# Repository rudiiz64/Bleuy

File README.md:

A design for a Bluetooth capable board.

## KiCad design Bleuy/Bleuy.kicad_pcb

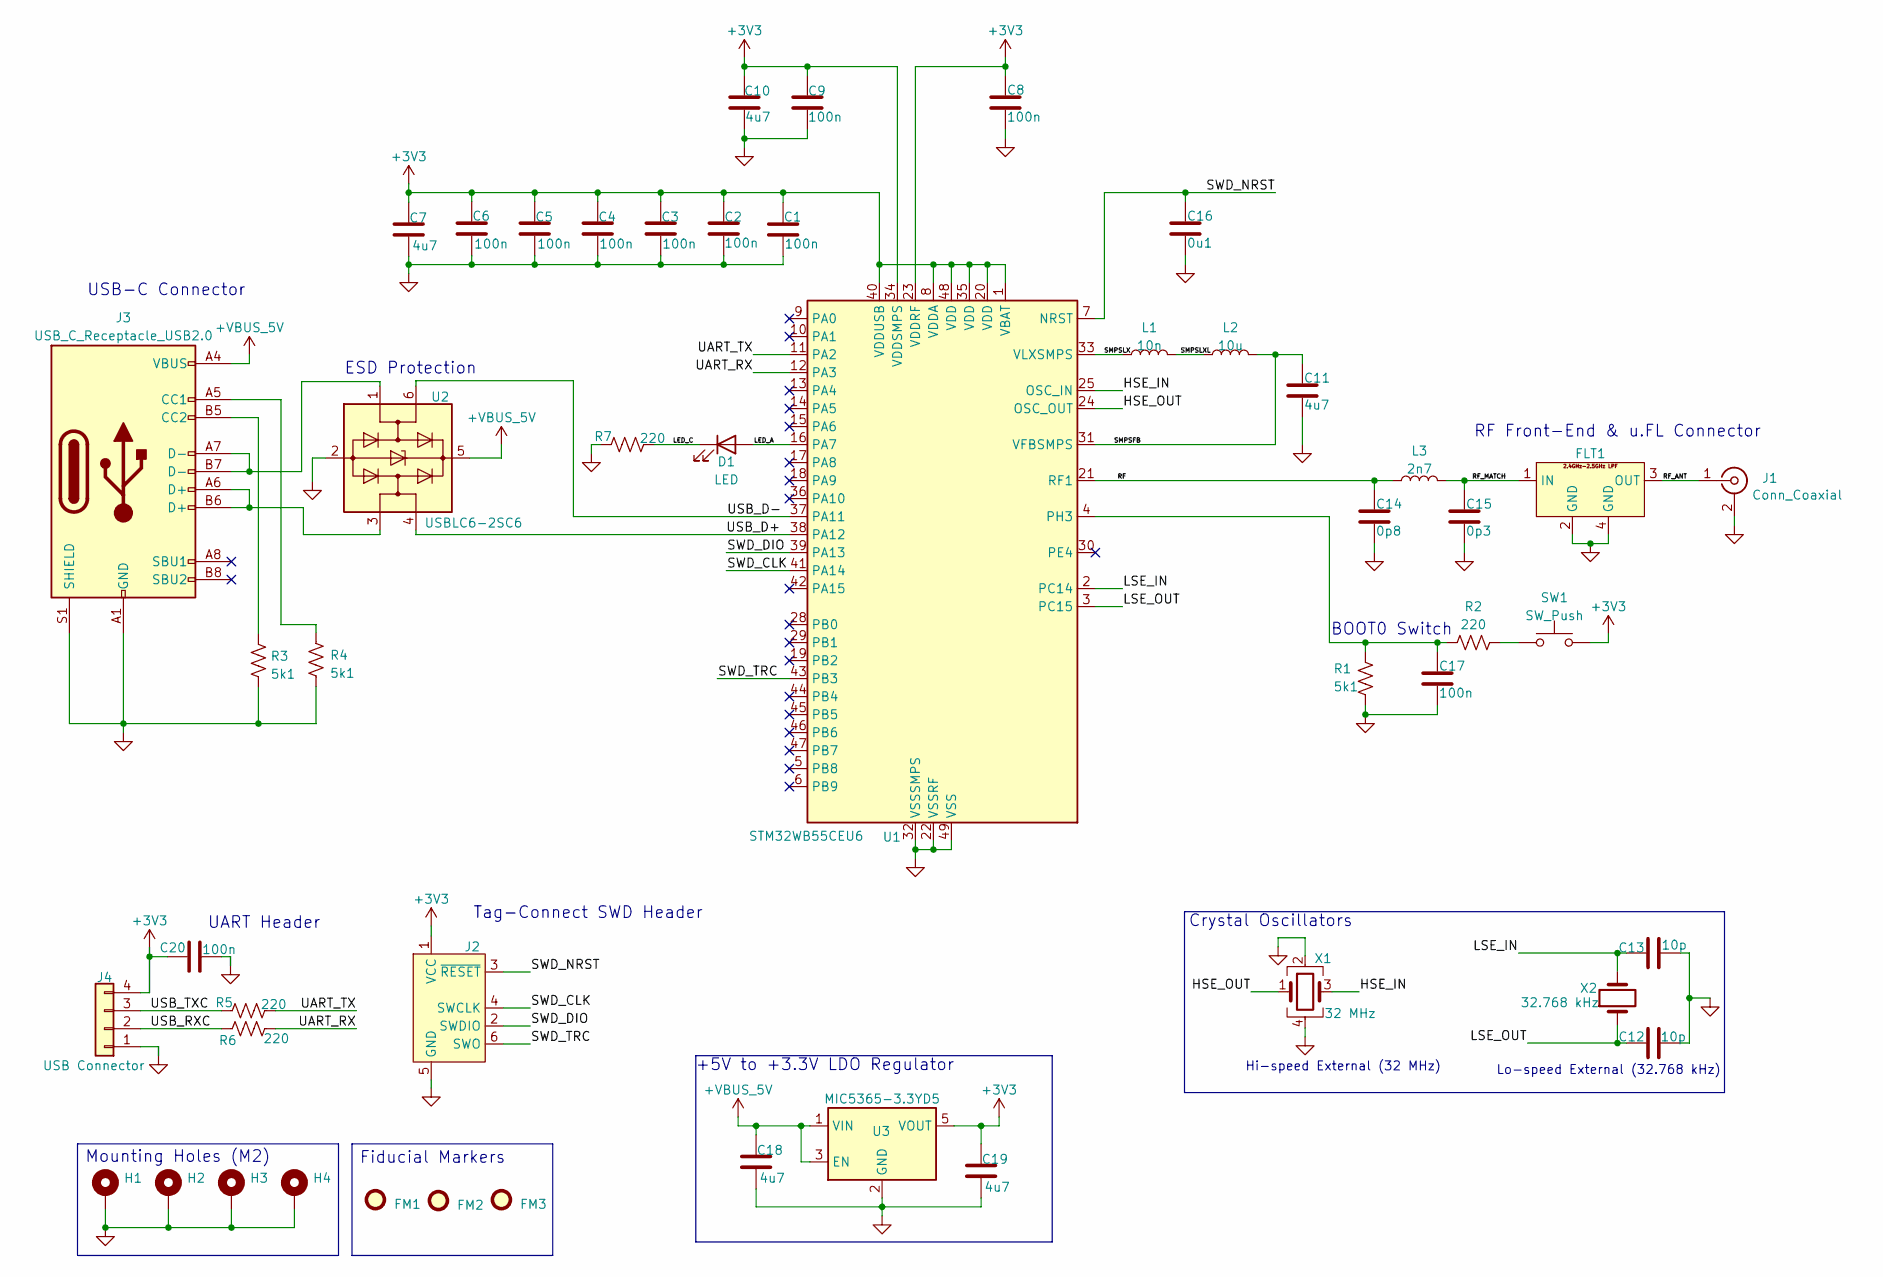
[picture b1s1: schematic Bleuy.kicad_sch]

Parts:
C1, C2, C3, C4, C5, C6, C8, C9, C17, C20: 100n; C_0402_1005Metric; Manufacturer Part Number 04023C104KAT2A
C7, C10, C11, C18, C19: 4u7; C_0603_1608Metric; Manufacturer Part Number 0603YD475MAT2A
C12, C13: 10p; C_0402_1005Metric; Manufacturer Part Number 04025A100JAT4A
C14: 0p8; C_0402_1005Metric; Manufacturer Part Number GRM1555C1HR80BA01D
C15: 0p3; C_0402_1005Metric; Manufacturer Part Number GRM1555C1HR30WA01D
C16: 0u1; C_0402_1005Metric; Manufacturer Part Number 04023C104KAT2A
D1: LED; LED_0402_1005Metric; Manufacturer Part Number 150040RS73240
FLT1: DLF162500LT-5028A1; Manufacturer Part Number DLF162500LT-5028A1
FM1, FM2, FM3: Fiducial; Fiducial_1mm_Mask2mm
H1, H2, H3, H4: MountingHole_Pad; MountingHole_2.2mm_M2_Pad_Via
J1: Conn_Coaxial; U.FL_Hirose_U.FL-R-SMT-1_Vertical; Manufacturer Part Number U.FL-R-SMT(01)
J2: Conn_ARM_SWD_TagConnect_TC2030; Tag-Connect_TC2030-IDC-FP_2x03_P1.27mm_Vertical
J3: USB_C_Receptacle_USB2.0; USB_C_Receptacle_GCT_USB4105-xx-A_16P_TopMnt_Horizontal; Manufacturer Part Number USB4105-GF-A
J4: USB Connector; Molex_PicoBlade_53261-0471_1x04-1MP_P1.25mm_Horizontal; Manufacturer Part Number 53048-0410
L1: 10n; L_0402_1005Metric; Manufacturer Part Number LQG15WZ10NJ02D
L2: 10u; L_0805_2012Metric; Manufacturer Part Number LQM21FN100M70L
L3: 2n7; L_0402_1005Metric; Manufacturer Part Number LQG15HS2N7S02
R1, R3, R4: 5k1; R_0402_1005Metric; Manufacturer Part Number RC0603FR-075K1L
R2, R5, R6, R7: 220; R_0402_1005Metric; Manufacturer Part Number RC0402FR-07221RL
SW1: SW_Push; SW_SPST_CK_RS282G05A3; Manufacturer Part Number RS282G05A3SMRT
U1: STM32WB55CEU6; QFN-48-1EP_7x7mm_P0.5mm_EP5.6x5.6mm; Manufacturer Part Number STM32WB55CEU6
U2: USBLC6-2SC6; SOT-23-6; Manufacturer Part Number USBLC6-2SC6
U3: MIC5365-3.3YD5; SOT-23-5; Manufacturer Part Number MIC5365-3.3YD5-TR
X1: 32 MHz; Crystal_SMD_2016-4Pin_2.0x1.6mm; Manufacturer Part Number NX2016SA-32M-EZS00A-CS06465
X2: 32.768 kHz; Crystal_SMD_2012-2Pin_2.0x1.2mm; Manufacturer Part Number NX2012SA-32.768K-STD-MUB-1

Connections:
+3V3: C1.1, C2.1, C3.1, C4.1, C5.1, C6.1, C7.1, C8.1, C9.1, C10.1, C19.1, C20.1, J2.1 (VCC), J4.4, SW1.2, U1.1 (VBAT), U1.8 (VDDA), U1.20 (VDD), U1.23 (VDDRF), U1.34 (VDDSMPS), U1.35 (VDD), U1.40 (VDDUSB), U1.48 (VDD), U3.5 (VOUT)
+5V: C18.1, J3.A4 (VBUS), J3.A9 (VBUS), J3.B4 (VBUS), J3.B9 (VBUS), U2.5 (VBUS), U3.1 (VIN), U3.3 (EN)
/HSE_IN: U1.25 (OSC_IN), X1.3
/HSE_OUT: U1.24 (OSC_OUT), X1.1
/LED_A: D1.2 (A), U1.16 (PA7)
/LED_C: D1.1 (K), R7.2
/LSE_IN: C13.1, U1.2 (PC14), X2.2
/LSE_OUT: C12.1, U1.3 (PC15), X2.1
/RF: C14.1, L3.1, U1.21 (RF1)
/RF_ANT: FLT1.3 (OUT), J1.1 (In)
/RF_MATCH: C15.1, FLT1.1 (IN), L3.2
/SMPSFB: C11.1, L2.2, U1.31 (VFBSMPS)
/SMPSLX: L1.1, U1.33 (VLXSMPS)
/SMPSLXL: L1.2, L2.1
/SWD_CLK: J2.4 (SWCLK), U1.41 (PA14)
/SWD_DIO: J2.2 (SWDIO), U1.39 (PA13)
/SWD_NRST: C16.1, J2.3 (~RESET), U1.7 (NRST)
/SWD_TRC: J2.6 (SWO), U1.43 (PB3)
/UART_RX: R6.2, U1.12 (PA3)
/UART_TX: R5.2, U1.11 (PA2)
/USB_D+: U1.38 (PA12), U2.4 (I/O2)
/USB_D-: U1.37 (PA11), U2.6 (I/O1)
/USB_RXC: J4.2, R6.1
/USB_TXC: J4.3, R5.1
GND: C1.2, C2.2, C3.2, C4.2, C5.2, C6.2, C7.2, C8.2, C9.2, C10.2, C11.2, C12.2, C13.2, C14.2, C15.2, C16.2, C17.2, C18.2, C19.2, C20.2, FLT1.2 (GND), FLT1.4 (GND), H1.1, H2.1, H3.1, H4.1, J1.2 (Ext), J2.5 (GND), J3.A1 (GND), J3.A12 (GND), J3.B1 (GND), J3.B12 (GND), J3.S1 (SHIELD), J4.1, R1.2, R3.2, R4.2, R7.1, U1.22 (VSSRF), U1.32 (VSSSMPS), U1.49 (VSS), U2.2 (GND), U3.2 (GND), X1.2, X1.4
unnamed: J3.A5 (CC1), R4.1
unnamed: J3.B5 (CC2), R3.1
unnamed: J3.A6 (D+), J3.B6 (D+), U2.3 (I/O2)
unnamed: J3.A7 (D-), J3.B7 (D-), U2.1 (I/O1)
unnamed: R2.2, SW1.1
unnamed: C17.1, R1.1, R2.1, U1.4 (PH3)

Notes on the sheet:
UART Header
Tag-Connect SWD Header
Mounting Holes (M2)
USB-C Connector
Crystal Oscillators
Lo-speed External (32.768 kHz)
+5V to +3.3V LDO Regulator
ESD Protection
BOOT0 Switch
Hi-speed External (32 MHz)
RF Front-End & u.FL Connector
Fiducial Markers

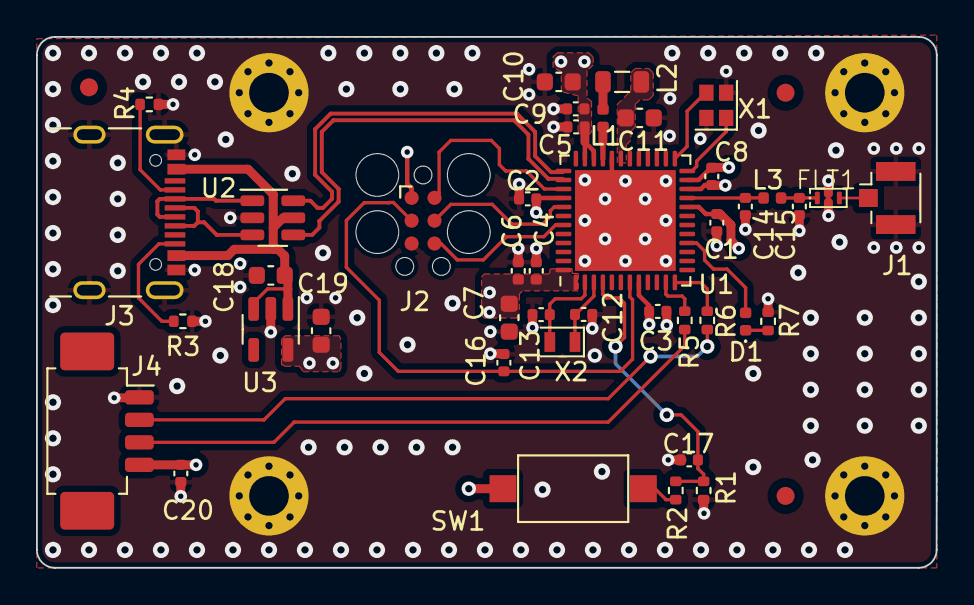
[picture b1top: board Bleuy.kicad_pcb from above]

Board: 4 copper layers, 50.0 x 29.5 mm, 49 parts (0 on the bottom side), 31 nets.

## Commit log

2023-12-18 Rev 0.1
    + Initial schematic creation
    + Added RF line
    + Added HSE and LSE osc
    + Added bypass+bulk caps to power pins
    + Added symbol for LPF
2023-12-19 Bleuy Rev A
    + Added USB-C receptacle to power implemented 5V to 3.3V LDO
    + Added footprint for LPF
    + Added tag-connect SWD pins and UART breakout pins
2024-01-02 Updated to Rev A Release
    + Finalized component placement
    + Added fiducial markers and mounting holes
    + Added ground stitching
    + Added power pours
    + Adjusted differential pair routing
    + Adjusted some routing to allow for better component placement
